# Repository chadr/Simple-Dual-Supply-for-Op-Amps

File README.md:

# Simple low noise Dual Supply for Op-Amp Learning

## What is this?
This is a simple, low noise, dual supply (+/Gnd/-) for use with prototyping Op-Amps like the venerable LM358/LM324. Specifically, it's meant to be used with IMSAI Guy's Op-Amp learning PCB. [Op Amp Test Board on PCBWay](https://www.pcbway.com/project/shareproject/Op_amp_Test_Board_77211aaf.html) It uses 2 x 9V (PP3) batteries for +/- 9V (or +/- 8.4V if lithiums are used).

<picture>
  
</picture>

## Bill of Materials (BoM)
| **Component** |             **Item**             |
|:-------------:|:--------------------------------:|
| Batt1, Batt2  | Eagle Plastics 12BH611-GR        |
| D1            | 5mm LED                          |
| R1            | 2.2K 1/4W                        |
| SW1           | CK JS202011CQN DPDT Straight     |
| J1            | 3 Position Screw Terminal 5.08mm |
| J2            | 2.54mm Pin Headers 3 Position    |

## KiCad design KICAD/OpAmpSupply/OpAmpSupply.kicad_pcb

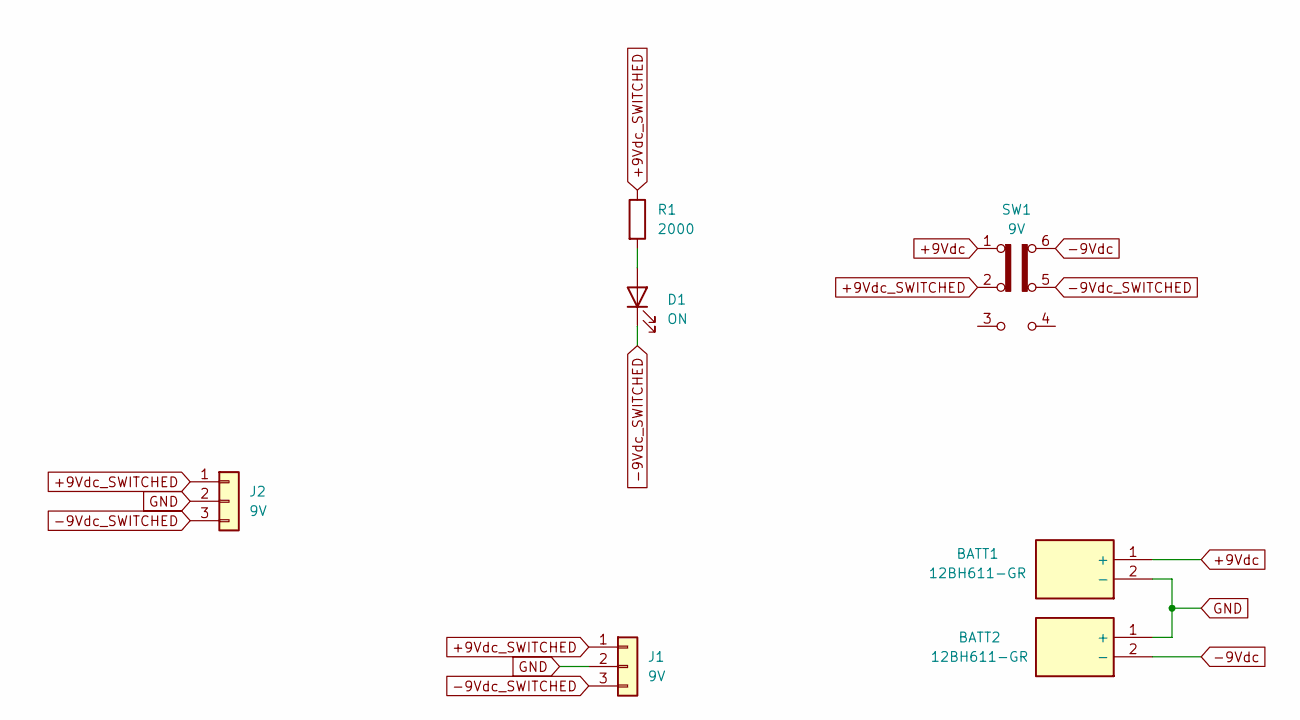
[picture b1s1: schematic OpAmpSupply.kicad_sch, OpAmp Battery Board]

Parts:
BATT1, BATT2: 12BH611-GR; 12BH611GR; Manufacturer_Part_Number 12BH611-GR; Mouser Part Number 12BH611-GR
D1: ON; LED_D5.0mm
J1: 9V; TerminalBlock_bornier-3_P5.08mm; Part Number 1-0301FBV0T
J2: 9V; PinHeader_1x03_P2.54mm_Vertical; Part Number 1-0301FBV0T
R1: 2000; R_Axial_DIN0207_L6.3mm_D2.5mm_P10.16mm_Horizontal
SW1: 9V; SW_CK_JS202011CQN_DPDT_Straight

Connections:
+9Vdc: BATT1.1 (+), SW1.1 (A)
+9Vdc_SWITCHED: J1.1, J2.1, R1.1, SW1.2 (B)
-9Vdc: BATT2.2 (-), SW1.6 (C)
-9Vdc_SWITCHED: D1.1 (K), J1.3, J2.3, SW1.5 (B)
GND: BATT1.2 (-), BATT2.1 (+), J1.2, J2.2
unnamed: D1.2 (A), R1.2

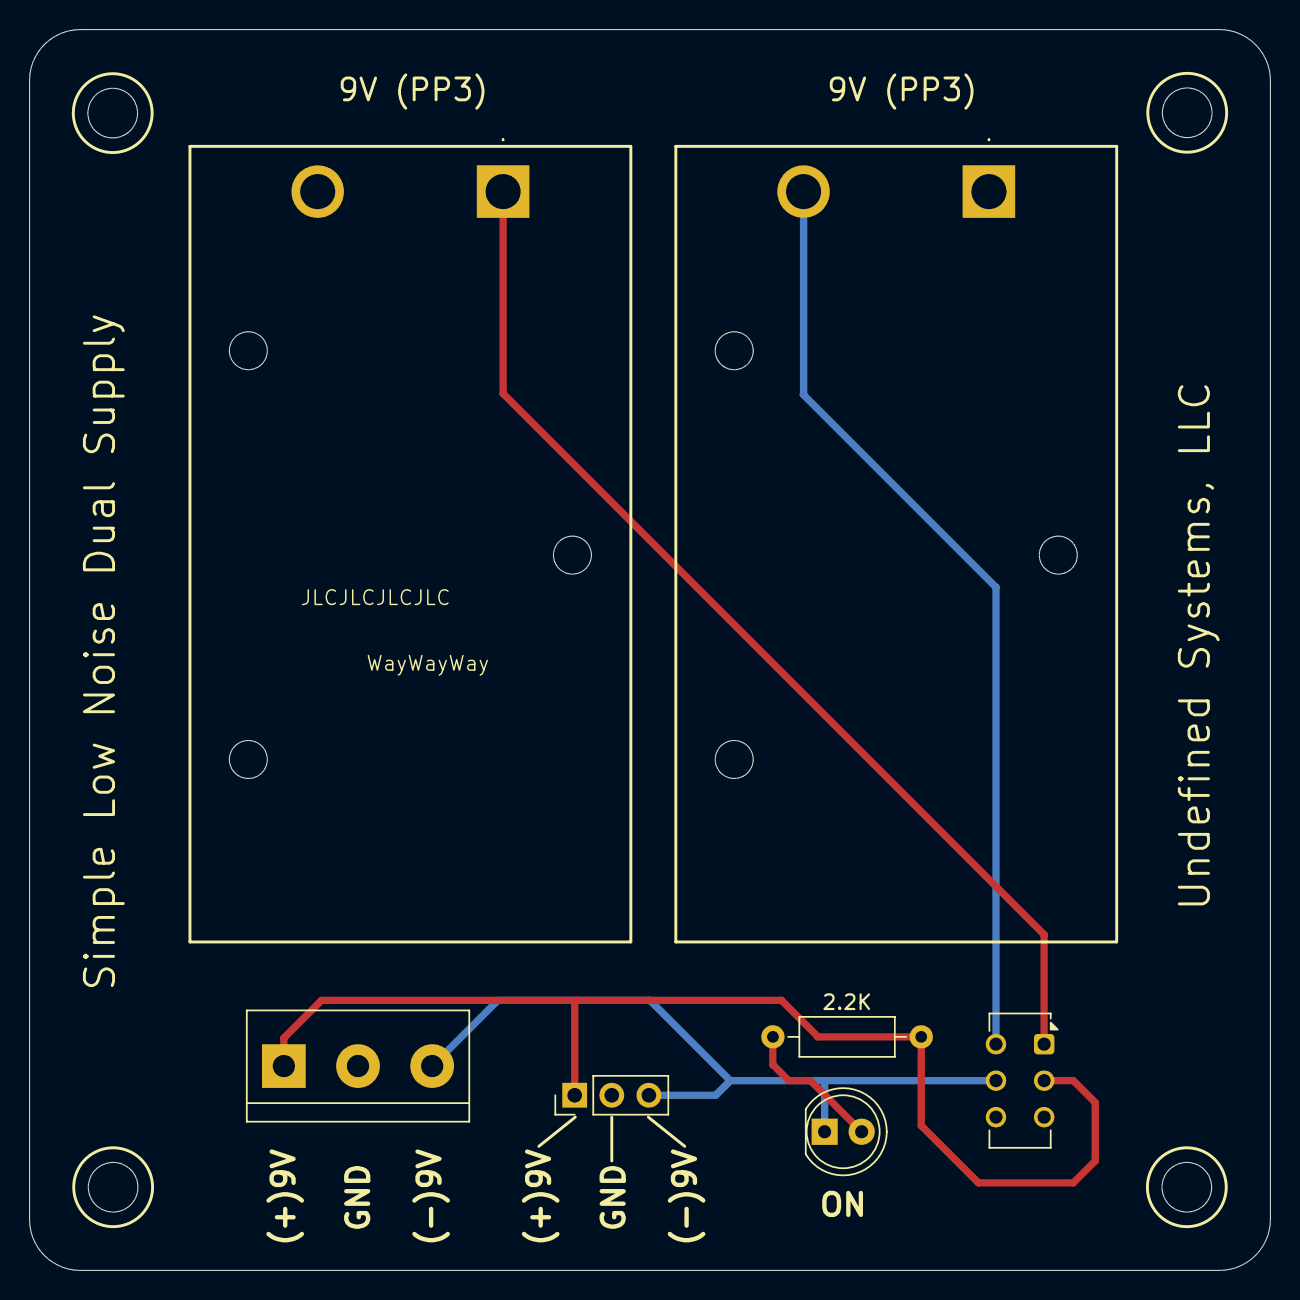
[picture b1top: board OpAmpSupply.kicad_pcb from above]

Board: 2 copper layers, 85.0 x 85.0 mm, 7 parts (0 on the bottom side), 6 nets.
